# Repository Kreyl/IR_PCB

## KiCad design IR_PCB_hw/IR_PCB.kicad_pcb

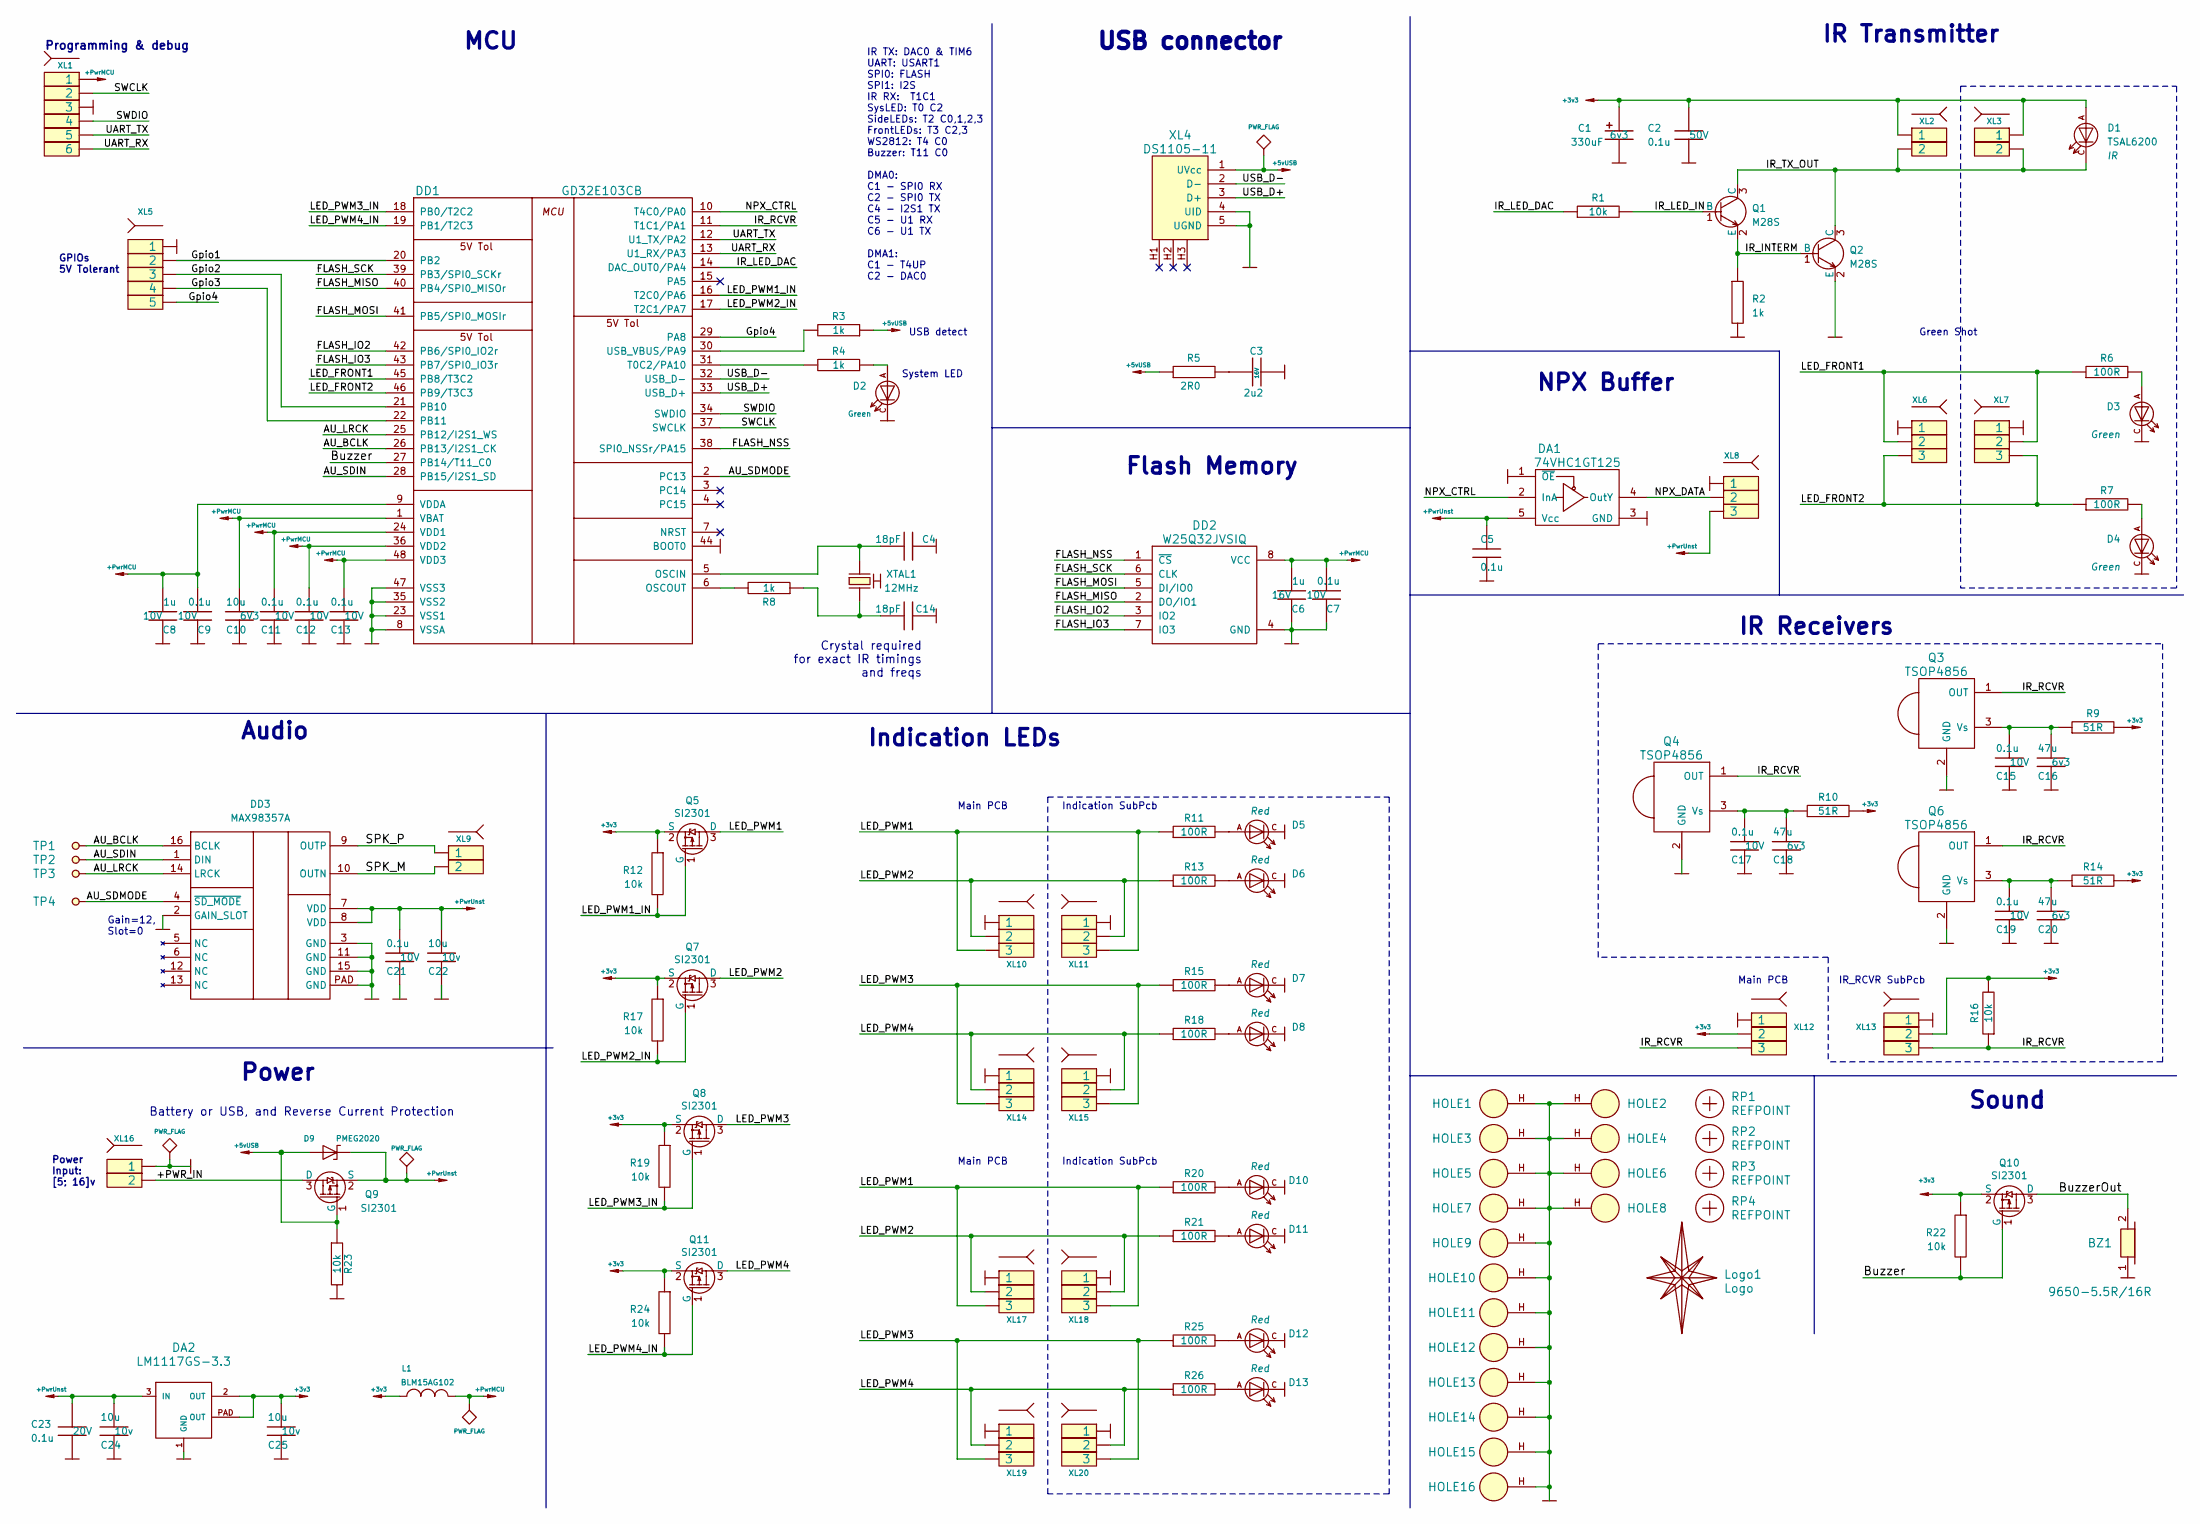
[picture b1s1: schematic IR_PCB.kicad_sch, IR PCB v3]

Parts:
BZ1: 9650-5.5R/16R; BUZZER_HC0903
C1: 330uF; CAP_D; Voltage 6v3
C2: 0.1u; CAP_0603_Silks; Tolerance 10%; Voltage 50V
C3: 2u2; CAP_0603_Silks; Tolerance 10%; Voltage 16V
C4, C14: 18pF; CAP_0603_Silks; Tolerance 5%; Voltage 50V
C5, C7, C9, C11, C12, C13, C15, C17, C19, C21: 0.1u; CAP_0603_Silks; Tolerance 20%; Voltage 10V
C6: 1u; CAP_0603_Silks; Tolerance 10%; Voltage 16V
C8: 1u; CAP_0603_Silks; Tolerance 10%; Voltage 10V
C10: 10u; CAP_0603_Silks; Tolerance 20%; Voltage 6V3
C16, C18, C20: 47u; CAP_1206; Tolerance 20%; Voltage 6v3
C22, C24, C25: 10u; CAP_0603_Silks; Tolerance 20%; Voltage 10v
C23: 0.1u; CAP_0603_Silks; Tolerance 20%; Voltage 20V
D1: TSAL6200; LED5mmR
D2: LTST-C191KGKT; LED_0603
D3, D4, D5, D6, D7, D8, D10, D11, D12, D13: LED5mmR
D9: PMEG2020; SOD323
DA1: 74VHC1GT125; SOT23-5
DA2: LM1117GS-3.3; SOT223
DD1: GD32E103CB; LQFP48
DD2: W25Q32JVSIQ; SO8_208MIL
DD3: MAX98357A; QFN-16_EP_3x3_Pitch0.5mm
HOLE1, HOLE2, HOLE3, HOLE4, HOLE5, HOLE6, HOLE7, HOLE8, HOLE9, HOLE10, HOLE11, HOLE12: HOLE_METALLED; Hole2d7_out4d2mm
HOLE13, HOLE14, HOLE15, HOLE16: HOLE_METALLED; Hole4_out5d3mm
L1: BLM15AG102; IND_0402_Fab; Tolerance 20%
Logo1: Logo; KiberiadaTYUKF
Q1, Q2: M28S; SOT23-3
Q3, Q4, Q6: TSOP4856; TSOP48xx
Q5, Q7, Q8, Q9, Q10, Q11: SI2301; SOT23-3
R1, R12, R16, R17, R19, R22, R23, R24: 10k; RES_0603_Silks; Tolerance 1%
R2, R3, R4, R8: 1k; RES_0603_Silks; Tolerance 1%
R5: 2R0; RES_0603_Silks; Tolerance 1%
R6, R7, R11, R13, R15, R18, R20, R21, R25, R26: 100R; RES_0603_Silks; Tolerance 1%
R9, R10, R14: 51R; RES_0603_Silks; Tolerance 1%
RP1, RP2, RP3, RP4: REFPOINT; REF_POINT_1MM
TP1, TP2, TP3, TP4: TESTPOINT; TESTPOINT_1MM
XL1: SOCKET_6; PLS-6-NoHole
XL2, XL9: SOCKET_2; SLD_2_2D5_SMD
XL3: SOCKET_2; PLS-2
XL4: DS1105-11; USBmicro_Connfly_DS1105-11
XL5: SOCKET_5; SLD_5_2D5_SMD
XL6, XL8, XL10, XL12, XL14, XL17, XL19: SOCKET_3; SLD_3_2D5_SMD
XL7, XL11, XL13, XL15, XL18, XL20: SOCKET_3; PLS-3
XL16: SOCKET_2; SLD_2_2D5
XTAL1: 12MHz; 03225C4

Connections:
+3v3: C1.1, C2.1, C25.1, D1.A, DA2.2 (OUT), DA2.PAD (OUT), L1.2, Q5.2 (S), Q7.2 (S), Q8.2 (S), Q10.2 (S), Q11.2 (S), R9.2, R10.2, R12.1, R14.2, R16.2, R17.1, R19.1, R22.1, R24.1, XL2.1, XL3.1, XL12.2, XL13.2
+5vUSB: D9.A, Q9.1 (G), R3.1, R5.1, R23.1, XL4.1 (UVcc)
+PwrMCU: C6.1, C7.1, C8.1, C9.1, C10.1, C11.1, C12.1, C13.1, DD1.1 (VBAT), DD1.9 (VDDA), DD1.24 (VDD1), DD1.36 (VDD2), DD1.48 (VDD3), DD2.8 (VCC), L1.1, XL1.1
+PwrUnst: C5.1, C21.1, C22.1, C23.1, C24.1, D9.C, DA1.5 (Vcc), DA2.3 (IN), DD3.7 (VDD), DD3.8 (VDD), Q9.2 (S), XL8.3
/+PWR_IN: Q9.3 (D), XL16.2
/AU_BCLK: DD1.26 (PB13/I2S1_CK), DD3.16 (BCLK), TP1.1
/AU_LRCK: DD1.25 (PB12/I2S1_WS), DD3.14 (LRCK), TP3.1
/AU_SDIN: DD1.28 (PB15/I2S1_SD), DD3.1 (DIN), TP2.1
/AU_SDMODE: DD1.2 (PC13), DD3.4 (~SD_MODE), TP4.1
/Buzzer: DD1.27 (PB14/T11_C0), Q10.1 (G), R22.2
/BuzzerOut: BZ1.2, Q10.3 (D)
/FLASH_IO2: DD1.42 (PB6/SPI0_IO2r), DD2.3 (IO2)
/FLASH_IO3: DD1.43 (PB7/SPI0_IO3r), DD2.7 (IO3)
/FLASH_MISO: DD1.40 (PB4/SPI0_MISOr), DD2.2 (DO/IO1)
/FLASH_MOSI: DD1.41 (PB5/SPI0_MOSIr), DD2.5 (DI/IO0)
/FLASH_NSS: DD1.38 (SPI0_NSSr/PA15), DD2.1 (~CS)
/FLASH_SCK: DD1.39 (PB3/SPI0_SCKr), DD2.6 (CLK)
/Gpio1: DD1.20 (PB2), XL5.2
/Gpio2: DD1.21 (PB10), XL5.3
/Gpio3: DD1.22 (PB11), XL5.4
/Gpio4: DD1.29 (PA8), XL5.5
/IR_INTERM: Q1.2 (E), Q2.1 (B), R2.1
/IR_LED_DAC: DD1.14 (DAC_OUT0/PA4), R1.1
/IR_LED_IN: Q1.1 (B), R1.2
/IR_RCVR: DD1.11 (T1C1/PA1), Q3.1 (OUT), Q4.1 (OUT), Q6.1 (OUT), R16.1, XL12.3, XL13.3
/IR_TX_OUT: D1.C, Q1.3 (C), Q2.3 (C), XL2.2, XL3.2
/LED_FRONT1: DD1.45 (PB8/T3C2), R6.1, XL6.2, XL7.2
/LED_FRONT2: DD1.46 (PB9/T3C3), R7.1, XL6.3, XL7.3
/LED_PWM1: Q5.3 (D), R11.1, R20.1, XL10.3, XL11.3, XL17.3, XL18.3
/LED_PWM1_IN: DD1.16 (T2C0/PA6), Q5.1 (G), R12.2
/LED_PWM2: Q7.3 (D), R13.1, R21.1, XL10.2, XL11.2, XL17.2, XL18.2
/LED_PWM2_IN: DD1.17 (T2C1/PA7), Q7.1 (G), R17.2
/LED_PWM3: Q8.3 (D), R15.1, R25.1, XL14.3, XL15.3, XL19.3, XL20.3
/LED_PWM3_IN: DD1.18 (PB0/T2C2), Q8.1 (G), R19.2
/LED_PWM4: Q11.3 (D), R18.1, R26.1, XL14.2, XL15.2, XL19.2, XL20.2
/LED_PWM4_IN: DD1.19 (PB1/T2C3), Q11.1 (G), R24.2
/NPX_CTRL: DA1.2 (InA), DD1.10 (T4C0/PA0)
/NPX_DATA: DA1.4 (OutY), XL8.2
/SPK_M: DD3.10 (OUTN), XL9.2
/SPK_P: DD3.9 (OUTP), XL9.1
/SWCLK: DD1.37 (SWCLK), XL1.2
/SWDIO: DD1.34 (SWDIO), XL1.4
/UART_RX: DD1.13 (U1_RX/PA3), XL1.6
/UART_TX: DD1.12 (U1_TX/PA2), XL1.5
/USB_D+: DD1.33 (USB_D+), XL4.3 (D+)
/USB_D-: DD1.32 (USB_D-), XL4.2 (D-)
unnamed: C3.1, R5.2
unnamed: C14.1, R8.1, XTAL1.2
unnamed: D2.A, R4.1
unnamed: D3.A, R6.2
unnamed: D4.A, R7.2
unnamed: D5.A, R11.2
unnamed: D6.A, R13.2
unnamed: D7.A, R15.2
unnamed: D8.A, R18.2
unnamed: D10.A, R20.2
unnamed: D11.A, R21.2
unnamed: D12.A, R25.2
unnamed: D13.A, R26.2
unnamed: C4.1, DD1.5 (OSCIN), XTAL1.1
unnamed: DD1.6 (OSCOUT), R8.2
unnamed: DD1.30 (USB_VBUS/PA9), R3.2
unnamed: DD1.31 (T0C2/PA10), R4.2
unnamed: C15.1, C16.1, Q3.3 (Vs), R9.1
unnamed: C17.1, C18.1, Q4.3 (Vs), R10.1
unnamed: C19.1, C20.1, Q6.3 (Vs), R14.1

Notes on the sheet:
Main PCB
Power Input: [5; 16]v
IR TX: DAC0 & TIM6 UART: USART1 SPI0: FLASH SPI1: I2S IR RX: T1C1 SysLED: T0 C2 SideLEDs: T2 C0,1,2,3 FrontLEDs: T3 C2,3 WS2812: T4 C0 Buzzer: T11 C0 DMA0: C1 - SPI0 RX C2 - SPI0 TX C4 - I2S1 TX C5 - U1 RX C6 - U1 TX DMA1: C1 - T4UP C2 - DAC0
IR_RCVR SubPcb
Power
Indication SubPcb
MCU
USB detect
Gain=12, Slot=0
NPX Buffer
System LED
Flash Memory
Battery or USB, and Reverse Current Protection
Crystal required for exact IR timings and freqs
Audio
Sound
Green Shot
USB connector
IR Transmitter
Programming & debug
IR Receivers
GPIOs 5V Tolerant
Indication LEDs

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
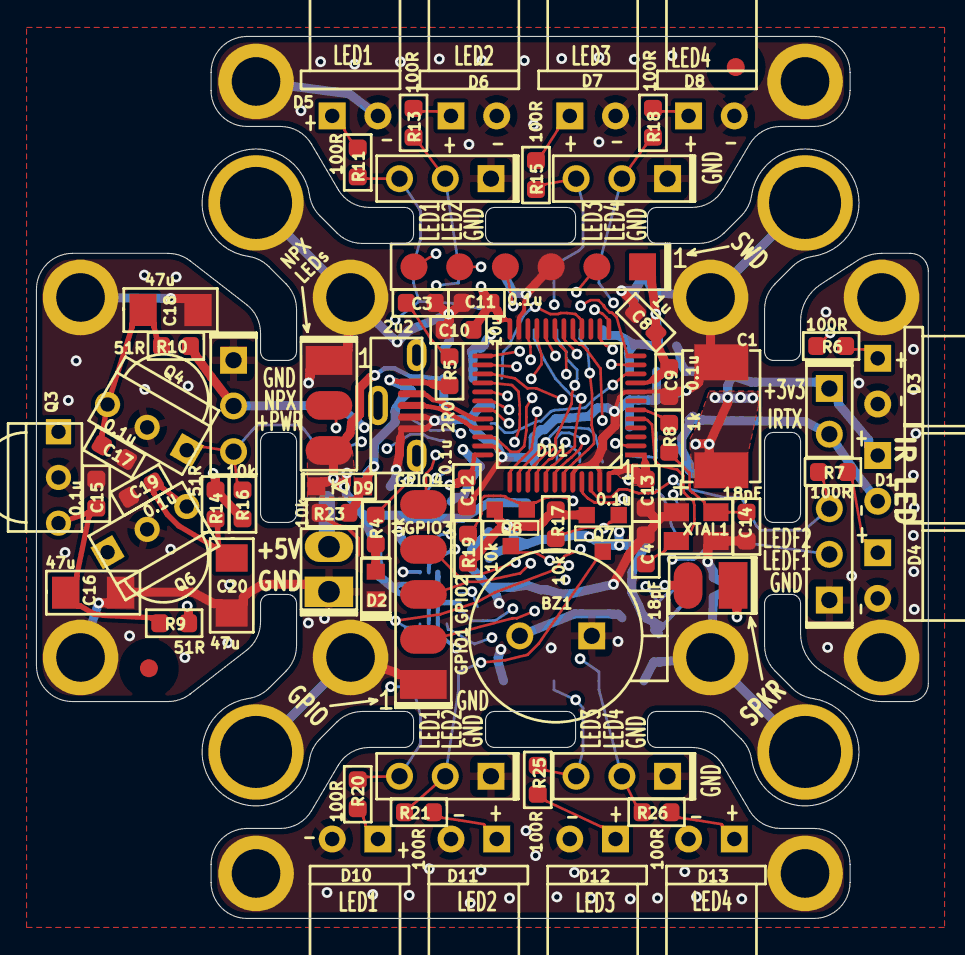
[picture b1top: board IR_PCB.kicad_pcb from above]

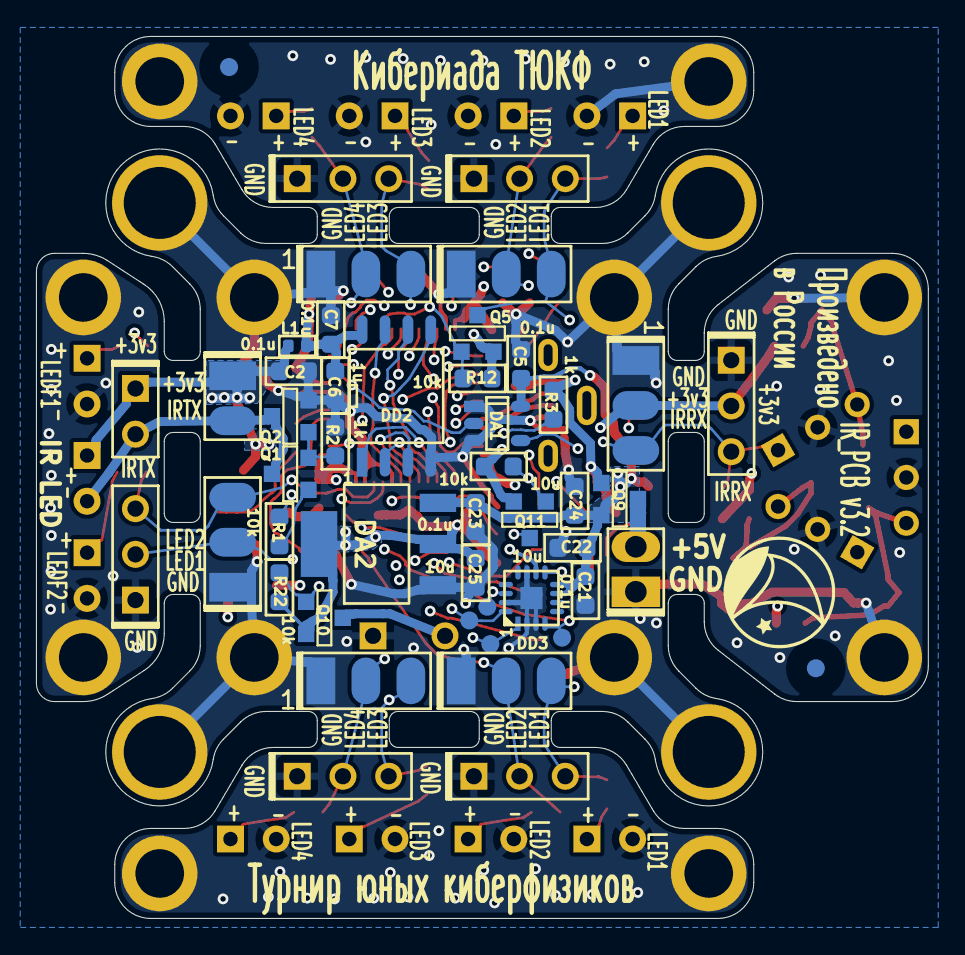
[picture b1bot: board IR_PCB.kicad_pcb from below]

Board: 4 copper layers, 49.5 x 49.0 mm, 128 parts (40 on the bottom side), 67 nets.

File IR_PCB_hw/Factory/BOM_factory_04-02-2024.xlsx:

Designator | Type | Value | PN | Footprint | Voltage | Description | Quantity | URL | Comment
BZ1 |  | 9650-5.5R/16R |  | Installation:BUZZER_HC0903 |  | Passive beeper | 1 | URL | DoNotMount
C1 |  | 330uF |  | Capacitors:CAP_D | 6v3 | Cap Tant Solid 330uF 6.3V D CASE | 1 | URL
C2, C5, C7, C9, C11, C12, C13, C15, C17, C19, C21, C23 | Capacitor SMD | 0.1u | CC0603KRX7R9BB104 | Capacitors:CAP_0603_Silks | 50V | X5R or X7R capacitor, 6.3V or higher | 12 | URL
C3 | Capacitor SMD | 2u2 | CL10A225KO8NNNC | Capacitors:CAP_0603_Silks | 16V | X5R or X7R capacitor, 6.3V or higher | 1 | URL
C4, C14 | Capacitor SMD | 18pF | CC0603JRNPO9BN180 | Capacitors:CAP_0603_Silks | 50V | NP0 capacitor, 6.3V or higher | 2 | URL
C6, C8 | Capacitor SMD | 1u | CL10A105KO8NNNC | Capacitors:CAP_0603_Silks | 16V | X5R or X7R capacitor, 6.3V or higher | 2 | URL
C10, C22, C24, C25 | Capacitor SMD | 10u | CL10A106MQ8NNNC | Capacitors:CAP_0603_Silks | 6V3 | X5R or X7R capacitor, 6.3V or higher | 4 | URL
C16, C18, C20 | Capacitor SMD | 47u | CL31A476MQHNNNE | Capacitors:CAP_1206 | 6v3 | X5R or X7R capacitor, 6.3V or higher | 3 | URL
D1 |  | TSAL6200 |  | LEDs:LED5mmR |  |  | 1 | URL | DoNotMount
D2 |  | LTST-C191KGKT | LTST-C191KGKT | LEDs:LED_0603 |  |  | 1 | URL
D3, D4, D5, D6, D7, D8, D10, D11, D12, D13 |  | ~ |  | LEDs:LED5mmR |  |  | 10 | URL | DoNotMount
D9 |  | PMEG2020 | PMEG2020AEA,115 | Diodes:SOD323 |  |  | 1 | URL
DA1 |  | 74VHC1GT125 | M74VHC1GT125DT1G | SOT:SOT23-5 |  |  | 1 | URL
DA2 |  | LM1117GS-3.3 |  | SOT:SOT223 |  |  | 1 | URL
DD1 |  | GD32E103CB |  | LQFP_TQFP:LQFP48 |  |  | 1 | URL
DD2 |  | W25Q32JVSIQ | W25Q32JVSSIQ | SO_DIL_TSSOP:SO8_208MIL |  |  | 1 | URL
DD3 |  | MAX98357A | MAX98357AETE+T | QFN_DFN:QFN-16_EP_3x3_Pitch0.5mm |  |  | 1 | URL
L1 | Inductor SMD | BLM15AG102 | BLM15AG102SN1D | Inductors:IND_0402_Fab |  | - | 1 | URL
Q1, Q2 |  | M28S |  | SOT:SOT23-3 |  |  | 2 | URL
Q3, Q4, Q6 |  | TSOP4856 |  | Sensors:TSOP48xx |  |  | 3 | URL | DoNotMount
Q5, Q7, Q8, Q9, Q10, Q11 |  | SI2301 |  | SOT:SOT23-3 |  | P-Chnl, 30v, 1.7A, 330mR@4.5v, Ciss=155pF | 6 | URL
R1, R12, R16, R17, R19, R22, R23, R24 | Resistor | 10k | RC0603FR-0710KL | Resistors:RES_0603_Silks |  | 1% resistor | 8 | URL
R2, R3, R4, R8 | Resistor | 1k | RC0603FR-071KL | Resistors:RES_0603_Silks |  | 1% resistor | 4 | URL
R5 | Resistor | 2R0 | RC0603FR-072RL | Resistors:RES_0603_Silks |  | 1% resistor | 1 | URL
R6, R7, R11, R13, R15, R18, R20, R21, R25, R26 | Resistor | 100R | RC0603FR-07100RL | Resistors:RES_0603_Silks |  | 1% resistor | 10 | URL
R9, R10, R14 | Resistor | 51R | RC0603FR-0751RL | Resistors:RES_0603_Silks |  | 1% resistor | 3 | URL
XL4 |  | DS1105-11 | DS1105-11-05SS8BNRS | Connectors:USBmicro_Connfly_DS1105-11 |  |  | 1 | URL
XTAL1 |  | 12MHz | SJK-7U-12.000-12-30-80-C-50 | Quartz:03225C4 |  |  | 1 | URL

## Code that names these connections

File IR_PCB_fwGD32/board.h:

/*
 * board.h
 *
 *  Created on: 28.08.2023
 *      Author: Kreyl
 */

#ifndef BOARD_H__
#define BOARD_H__

// ==== General ====
#define BOARD_NAME          "IR_PCBv2"
#define APP_NAME            "IR_PCB"

#ifndef TRUE
#define TRUE    1
#endif
#ifndef FALSE
#define FALSE   0
#endif

// Freq of external crystal if any. Leave it here even if not used.
#define CRYSTAL_FREQ_HZ             12000000UL

#if 1 // ==== MCU info ====
// Configuration of the Cortex-M4 processor and core peripherals
#define __CM4_REV                   0x0001   // Core revision r0p1
#define __MPU_PRESENT               0        // GD32E11x do not provide MPU
#define CORTEX_SIMPLIFIED_PRIORITY  FALSE
#define CORTEX_PRIORITY_BITS        4        // GD32E11x uses 4 bits for the priority levels
#define __FPU_PRESENT               1        // FPU present

#define CORTEX_USE_FPU              __FPU_PRESENT
#define CORTEX_MODEL                4
#endif

#if 1 // ==== OS timer settings ====
#define SYS_TIM                     TIM10
#define SYS_TIM_IRQn                TIMER0_TRG_CMT_TIMER10_IRQn
#define SYS_TIM_IRQ_HANDLER         TIMER0_TRG_CMT_TIMER10_IRQHandler
#define SYS_TIM_IRQ_PRIORITY        2
#endif

#if 1 // ========================== GPIO =======================================
// EXTI
#define INDIVIDUAL_EXTI_IRQ_REQUIRED    FALSE

// User GPIOs. Hardware-dependent.
#define Gpio1           PB2
#define Gpio2           PB10
#define Gpio3           PB11
#define Gpio4           PA8

// Usage by app
//#define Output_PulseOnHit
#define Output_HitsPresent  Gpio3
#define Input_BurstFire     Gpio2, Gpio::PullDown
#define Input_SingleFire    Gpio1, Gpio::PullDown
#define INPUT_DEADTTIME_ms  36
// PWM Input
#define INPUT_PWM           PA8, Gpio::PullDown, TIM0
#define INPUT_PWM_TMR_IRQ   TIMER0_Channel_IRQn
#define INPUT_PWM_TMR_IRQ_HNDLR TIMER0_Channel_IRQHandler
#define INPUT_PWM_CHECK_PERIOD_ms       27 // It is timeout, too. After this period of pulse absense there will be event of Duty=0
#define PWM_DUTY_SINGLE_FIRE_percent    33L
#define PWM_DUTY_BURST_FIRE_percent     66L
#define PWM_DUTY_DEVIATION_percent      9L // PWM is considered unchanged if the change is less than this value

// UART
#define UART_TX_PIN     PA2
#define UART_RX_PIN     PA3

// Green LED
#define LUMOS_PIN       PA10, Gpio::PushPull

// Front LEDs
#define LED_FRONT1      { PB8, TIM3, 2, invNotInverted, Gpio::PushPull, 255 }
#define LED_FRONT2      { PB9, TIM3, 3, invNotInverted, Gpio::PushPull, 255 }
#define FRONT_LEDS_CNT  2

// Side LEDs
#define LED_PWM1        { PA6, TIM2, 0, invInverted, Gpio::PushPull, 255 }
#define LED_PWM2        { PA7, TIM2, 1, invInverted, Gpio::PushPull, 255 }
#define LED_PWM3        { PB0, TIM2, 2, invInverted, Gpio::PushPull, 255 }
#define LED_PWM4        { PB1, TIM2, 3, invInverted, Gpio::PushPull, 255 }
#define SIDE_LEDS_CNT   4

// Neopixel LEDs
#define NPX_PARAMS      PA0, TIM4, 0

// Beeper
#define BEEPER_TOP      22 // 22 < 255: needed to increase frequency
#define BEEPER_PIN      { PB14, TIM11, 0, invInverted, Gpio::PushPull, BEEPER_TOP }

// IR LED
#define IR_LED          PA4 // DAC
#define IR_BIT_CNT_MAX  16L // Just for buffer reservation

// IR Rcvr
#define IR_RX_DATA_PIN  PA3

// Spi Flash
#define FLASH_NSS       PA15
#define FLASH_SCK       PB3
#define FLASH_MISO      PB4
#define FLASH_MOSI      PB5
#define FLASH_IO2       PB6
#define FLASH_IO3       PB7

// Audio
#define AU_SPI          SPI1
#define AU_SDMODE       PC13
#define AU_LRCK         PB12
#define AU_BCLK         PB13
#define AU_SDIN         PB15

#endif // GPIO

#if 1 // ========================= Timer =======================================
// IR LED
#define TMR_DAC_SMPL        TIM6
// IR Receiver
#define TMR_IR_RX           TIM1
#define TMR_IR_RX_IRQ       TIMER1_IRQn
#define TMR_IR_RX_IRQ_HNDLR TIMER1_IRQHandler
#endif // Timer

#if 1 // ==== USB ====
#define USB_SOF_CB_EN       FALSE // SOF callback not used
#define USB_IRQ_PRIO        14
#define USB_TXBUF_CNT       16   // 16 buffers of size=EP_BULK_SZ=64 each results in 1024 bytes total
// Crystalless mode: IRC48M utilized, it syncs using SOF pulses at PA8. Therefore, PA8 is occupied.
#define USB_CRYSTALLESS_EN  TRUE
// Next options: set to 1U if enabled, 0U if disabled. Required for Setup Request reply.
#define USB_REMOTE_WKUP_EN  0U
#define USB_SELF_POWERED    0U  // if not self powered, then it is bus powered
// Hardware depended, do not touch
#define USB_SET_ADDRESS_ACK_BY_HW   FALSE
#define USB_SEQUENCE_WORKAROUND     TRUE    // XXX CheckMe
#define USB_SET_ADDR_AFTER_ZEROPKT  FALSE
#define USB_NUM_EP_MAX              3U // Excluding Ep0
#define USB_IRQ_HANDLER             USBFS_IRQHandler // 0x14C
#define USB_IRQ_NUMBER              USBFS_IRQn // 67

#endif

#if 1 // =========================== I2C =======================================
#define I2C0_ENABLED    FALSE
#define I2C1_ENABLED    FALSE

#define I2C_BAUDRATE_HZ 400000UL
#define I2C_DUTYCYC     I2C_DUTYCYCLE_2
#endif

#if 1 // ======================== Inner ADC ====================================
#define ADC_REQUIRED    FALSE

#endif

#if 1 // =========================== DMA =======================================
// SPI FLASH
#define SPIFLASH_DMA_RX     DMA0_Channel1
#define SPIFLASH_DMA_TX     DMA0_Channel2
// Audio
#define I2S_DMA_TX          DMA0_Channel4
// Uart
#define UART_DMA_RX         DMA0_Channel5
#define UART_DMA_TX         DMA0_Channel6
// Npx LEDs
#define NPX_DMA             DMA1_Channel1 // Tim4 Update
// DAC
#define DAC_DMA             DMA1_Channel2

#endif // DMA

#if 1 // ========================== USART ======================================
//#define PRINTF_FLOAT_EN TRUE
#define UART_TXBUF_SZ   2048
#define UART_RXBUF_SZ   128
#define CMD_BUF_SZ      128
#define UART_RX_POLL_MS 99

#define CMD_UART        USART1

#define CMD_UART_PARAMS CMD_UART, UART_TX_PIN, UART_RX_PIN, UART_DMA_TX, UART_DMA_RX

#endif

#endif //BOARD_H__

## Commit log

2023-08-04 Sch started
2023-08-04 Sch in progress
2023-08-05 Layout done
2023-08-05 Silks done
2023-08-05 Sent to factory
2023-08-05 + BOM
2023-08-11 + FW UART works
2023-08-12 LEDs work
2023-08-14 State machines started
2023-08-14 In progress
2023-08-16 IR tx layer works
2023-08-16 Firing seems ok
2023-08-16 Minor clean-up
2023-08-16 Clean-up
2023-08-16 IR RX low level works
2023-08-17 IR RX works
2023-08-17 * Single pkt per shot * GunID added * Hit counting system works
2023-08-17 Indication seems done
2023-08-18 Settings save/load Infinite conditions processed
2023-08-18 Inputs and outputs work
2023-08-18 Pkt type added to settings
2023-08-18 Working with sounds
2023-08-19 + bootloader
2023-08-19 Bootloader prepared
2023-08-19 + Bootloader works
2023-08-19 Release
2023-09-12 IR protocol changed to OpenLaserTag
2023-10-04 Layout started
2023-10-07 Layout in progress
2023-10-08 PCBv3 sent to factory
2023-10-16 PCB v 3.1
2023-10-17 working on bom
2023-10-18 BOM constructed
2023-10-23 + Factory BOM
2023-10-23 + PCB desc
2023-10-24 Replace USB conn with micro one Replace 0402 wit 0603
2023-10-25 RTOS, UART, XTAL work
2023-10-25 SPI in progress
2023-10-26 Working on SpiFlash
2023-10-26 Flash in Quad mode works ok
2023-10-26 + Basesequencer
2023-10-27 Add beeper
2023-10-28 ADC in progress
2023-10-28 ADC again
2023-10-28 Working on DAC
2023-10-28 IR TX works
2023-10-28 ir RX seems working, but last bit is corrupted
2023-10-29 IR RX ok first steps to Npx
2023-10-30 + NPX transmit works + Sound works, but starts to blink
2023-10-30 Refactor
2023-10-30 Usb conn moved
2023-10-30 ADC is not working
2023-10-30 PCB v3.2 Routing done, cleanup done
2023-10-31 ADC works
2023-11-10 Switching to CDC+MSD
2023-11-14 Working on MsdCdc
2023-11-15 Serial & MSD work by usb, but FLASH is still not implemented.
2023-11-15 Fighting with Flash read
2023-11-16 Fix bug with timer init instead of alarm stop
2023-11-16 Clean-up and refactoring
2023-11-17 + Boot
2023-11-17 Bootloader in progress
2023-11-21 Bootloader seem ok
2023-11-21 Bootloader resets everything before jumping
2023-11-24 Testing works
2023-11-24 + Add App + Add settings + Add pin IRQ & EXTI
2023-11-24 * Allow damage from player with same ID, but other team
2023-11-24 + Add reboot to bootloader
2023-11-28 + Testing functionality
2023-11-29 + First version binary
2023-12-09 Reply to command to where it came from (USB in general), not debug UART
2023-12-10 * Fix USB CDC bug, which leads to failures during printing * Testing disables app * Refactor MSD SCSI
2023-12-10 Add full release
2024-01-10 Flame works somehow
2024-01-13 + IR TX frequency made parametric in settings + Help on commands available
2024-02-01 + .pos file
2024-02-04 Preparation for factory
2024-02-28 Fixed: values in form '0x8305' now read from settings.ini successfully
2024-04-18 Refactoring
2024-04-19 W25Q64 memory implemented
2024-04-19 Spi Flash added to boot
2024-04-19 + Full hex
2024-06-10 + Watchdog * Minor refactoring
2024-06-10 + Flame len set by cmd RC
2024-06-11 + start/stop
2024-06-30 Huge refactoring + PWM input works
2024-07-01 Working on setiings
2024-07-02 Working on зле rx
2024-07-03 + PktType made more informative + Add Rounds implemented
2024-07-04 + pkt printing
2024-08-25 + IR RX timings put to settings
2024-08-29 + for Orion
2024-08-31 + IR tx command
2024-08-31 + Fire, Burst, Stop commands + SuperDamageID + IR repeat
2024-09-02 working on pin mode select
2024-09-02 + RetvVal
2024-09-02 + Custom OutPin
2024-09-04 + FireAlways setting
2024-09-05 Saving settings moved from special function to generalized one
2024-09-05 16 bit shot pkt allowed
2024-09-05 Remove too deep inheritance in Settings.
2024-09-08 deep inheritance seem working
2024-09-09 still bad
2024-09-09 Minor refactoring
2024-10-03 Refactoring + Set Step
2024-10-04 Huge refactoring
2024-12-05 More Huge Refactorig
2024-12-06 Seems to work somehow
2025-03-05 Proceeding
2025-03-05 Settings loaded ok
2025-03-05 Custom rx pkt added to apply SuperDamage
2025-03-05 UART buf increased to 3000 chars
2025-03-05 +bin
2025-03-05 syncing
2025-03-05 minor changes
